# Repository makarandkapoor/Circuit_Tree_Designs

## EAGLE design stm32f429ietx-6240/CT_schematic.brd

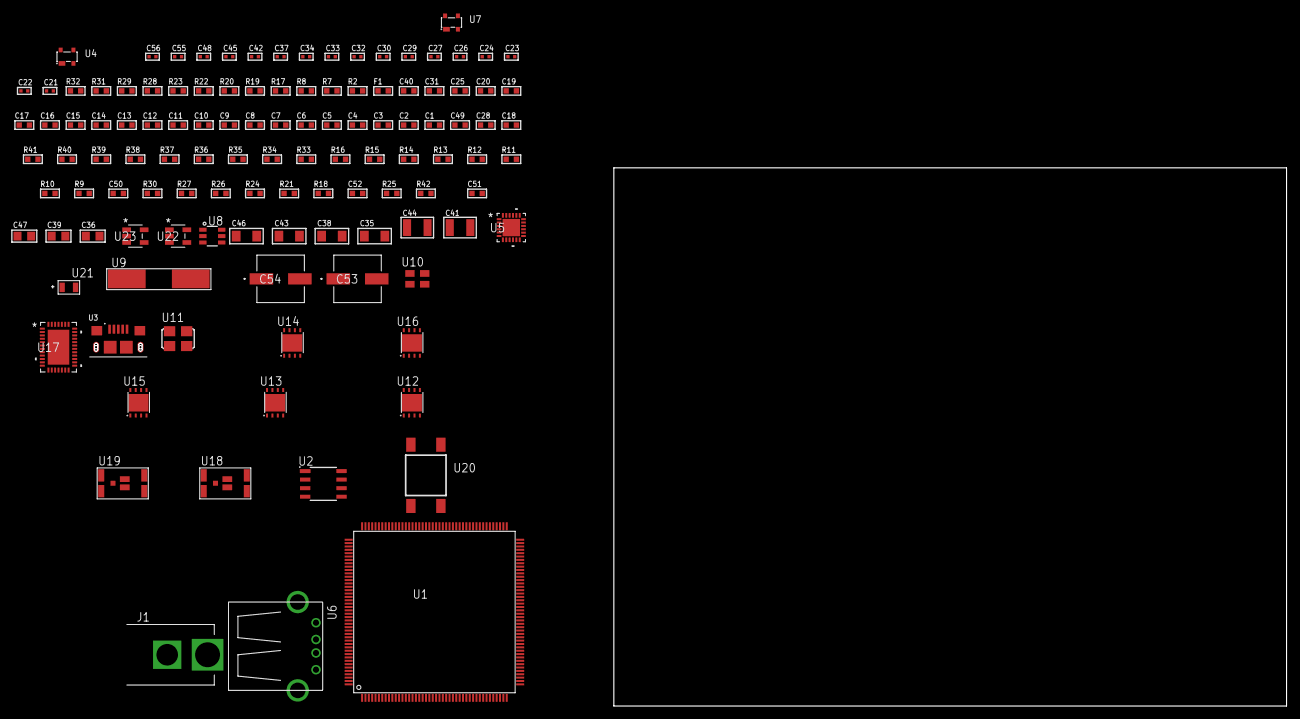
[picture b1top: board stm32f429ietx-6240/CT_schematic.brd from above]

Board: 2 copper layers, 118 parts (0 on the bottom side), 79 nets, no tracks yet.

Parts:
C1, C20, C25, C40: 1e-06; C0603
C2, C3, C4, C5, C6, C7, C8, C9, C10, C11, C12, C13, C14, C15, C16, C17: 1e-07; C0603
C18: 4.7e-06; C0603
C19: 1e-08; C0603
C21, C22, C48: 1e-07; C0402
C23, C24: 1e-11; C0402
C26, C27, C29, C30, C32, C33, C34, C37, C42, C45, C55, C56: 1e-08; C0402
C28, C49: 2.2e-06; C0603
C31: 0.0001; R0603
C35, C38, C43, C46: 1e-05; C1206
C36, C39, C47: 1e-05; C0805
C41, C44: 1e-05; C1210
C50: 2.45e-08; R0603
C51: 2.8258362168397e-09; R0603
C52: 7.105e-09; R0603
C53, C54: 0.0001; EXV-9H
F1: 240.0; L0603
J1: PJ-037B; PJ-037B_PACKAGE
R2, R20, R23, R29, R32: 1000.0; R0603
R7, R8: 4700.0; R0603
R9, R10, R11, R12, R13, R14, R15, R33, R35, R36, R39, R40, R41: 10000.0; R0603
R16: 47000.0; R0603
R17: 8060.0; R0603
R18, R21, R24, R26, R27, R30: 100000.0; R0603
R19, R31: 200.0; R0603
R22: 806.0; R0603
R25: 153694.38; R0603
R28: 3900.0; R0603
R34: 75000.0; R0603
R37, R38: 95300.0; R0603
R42: 65036.363636364; R0603
U1: STM32F429IET6; LQFP176
U2: AT25M02-SSHD-T; SOIC-8
U3: 10118193-0001LF; FCI_10118193-0001LF
U4, U7: prtr5v0u2ax; SOT143B
U5: USB3317C-CP-TR; QFN-24
U6: 61400416021; USB-A-H
U8: MAX4995AAUT+T; SOT-23-6
U9: ABLS-25.000MHZ-B2F-T
U10: ASEK-32.768KHz-ECST; ASEK
U11: ASFL1-26MHZ-NCS; ASFL1
U12, U13, U15, U16: LP3878SDX-ADJ/NOPB; WSON-8
U14: LP2951ACSDX/NOPB; WSON-8
U17: LTC2928CUHF#PBF; QFN-38_UHF
U18, U19: IRF8306MTRPbF; IRF8306MTRPBF
U20: 4-1437565-2; SW_4-1437565-2
U21: Q65110A2395; LGM67K-G1J2-24-Z
U22, U23: nc7sz125m5x; NC7SZ125M5X

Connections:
CLK_CRYSTAL_U1_29: C23.1, U1.29, U9.1
CLK_CRYSTAL_U1_30: C24.1, U1.30, U9.2
CLK_U1_9: U1.9, U10.3
CLK_U5_23: U5.23, U11.3
GND: C1.2, C2.2, C3.2, C4.2, C5.2, C6.2, C7.2, C8.2, C9.2, C10.2, C11.2, C12.2, C13.2, C14.2, C15.2, C16.2, C17.2, C18.2, C19.2, C20.2, C21.2, C22.2, C23.2, C24.2, C25.2, C26.2, C27.2, C28.2, C29.2, C30.2, C31.2, C32.2, C33.2, C34.2, C35.2, C36.2, C37.2, C38.2, C39.2, C40.2, C41.2, C42.2, C43.2, C44.2, C45.2, C46.2, C47.2, C48.2, C49.2, C50.2, C51.2, C52.2, C53.2, C54.2, C55.2, C56.2, J1.2, R2.2, R11.2, R16.2, R17.2, R20.2, R23.2, R26.2, R29.2, R32.2, R34.2, R37.2, R38.2, R39.2, R40.2, R41.2, U1.14, U1.22, U1.37, U1.61, U1.71, U1.90, U1.102, U1.113, U1.122, U1.126, U1.135, U1.148, U1.158, U2.4, U3.5, U3.6, U3.7, U3.8, U3.9, U4.1, U5.1, U5.25, U6.4, U6.5, U6.6, U7.1, U8.2, U10.2, U11.2, U12.3, U12.PAD, U13.3, U13.PAD, U14.3, U14.4, U14.PAD, U15.3, U15.PAD, U16.3, U16.PAD, U17.8, U17.9, U17.10, U17.12, U17.13, U17.24, U17.25, U17.30, U17.32, U17.39, U21.C, U22.1, U22.3, U23.1, U23.3
NET_U1_31: R7.1, U1.31, U22.4
NET_U1_39: C19.1, C20.1, F1.1, U1.38, U1.39
NET_U1_48: R12.1, U1.48
NET_U1_58: R11.1, U1.58
NET_U1_125: C22.1, U1.125
NET_U1_166: R10.1, U1.166
NET_U1_171: R9.1, U1.171
NET_U1_176: U20.3, U20.4
NET_U2_3: R13.1, U2.3
NET_U2_7: R15.1, U2.7
NET_U5_4: C28.1, U5.4
NET_U5_22: R8.1, U5.22, U23.4
NET_U5_24: R17.1, U5.24
NET_U6_1: C31.1, U5.2, U6.1, U7.4, U8.1
NET_U6_2: U5.5, U6.2, U7.3
NET_U6_3: U5.6, U6.3, U7.2
NET_U8_3: R16.1, U8.3
NET_U8_4: U5.7, U8.4
NET_U12_1: C34.1, U12.1
NET_U12_6: R19.2, R20.1, U12.6
NET_U12_8: R18.1, U12.8
NET_U13_1: C37.1, U13.1
NET_U13_6: R22.2, R23.1, U13.6
NET_U13_8: R21.1, U13.8
NET_U14_5: R24.1, U14.5
NET_U14_7: R25.2, R26.1, U14.7
NET_U15_1: C42.1, U15.1
NET_U15_6: R28.2, R29.1, U15.6
NET_U15_8: R27.1, U15.8
NET_U16_1: C45.1, U16.1
NET_U16_6: R31.2, R32.1, U16.6
NET_U16_8: R30.1, U16.8
NET_U17_3: R40.1, U17.3
NET_U17_6: R37.1, U17.6
NET_U17_7: R38.1, U17.7
NET_U17_16: R39.1, R42.1, U17.16
NET_U17_18: R36.1, U17.18
NET_U17_19: R35.1, U17.19, U17.20
NET_U17_21: R33.1, R34.1, U17.21, U22.2, U23.2
NET_U17_22: C48.1, R33.2, R35.2, R36.2, U17.11, U17.22
NET_U17_26: C51.1, U17.26
NET_U17_27: C50.1, U17.27
NET_U17_28: C52.1, U17.28
NET_U17_38: R41.1, U17.38
NET_U18_3: U17.2, U18.3
NET_U19_3: U17.37, U19.3
NET_U20_1: R2.1, U20.1, U20.2
PROC_SPI1_MISO: U1.52, U2.2
PROC_SPI1_MOSI: U1.53, U2.5
PROC_SPI1_NSS: R14.1, U1.50, U2.1
PROC_SPI1_SCK: U1.161, U2.6
PROC_USB_OTG_FS_DM: U1.122, U3.2, U4.3
PROC_USB_OTG_FS_DP: U1.123, U3.3, U4.2
PROC_USB_OTG_FS_VBUS: C25.1, U1.120, U3.1, U4.4
PROC_USB_OTG_HS_ULPI_CK: U1.51, U5.12
PROC_USB_OTG_HS_ULPI_D0: U1.47, U5.16
PROC_USB_OTG_HS_ULPI_D1: U1.56, U5.15
PROC_USB_OTG_HS_ULPI_D2: U1.57, U5.14
PROC_USB_OTG_HS_ULPI_D3: U1.79, U5.13
PROC_USB_OTG_HS_ULPI_D4: U1.80, U5.11
PROC_USB_OTG_HS_ULPI_D5: U1.92, U5.10
PROC_USB_OTG_HS_ULPI_D6: U1.93, U5.9
PROC_USB_OTG_HS_ULPI_D7: U1.163, U5.8
PROC_USB_OTG_HS_ULPI_DIR: U1.13, U5.19
PROC_USB_OTG_HS_ULPI_NXT: U1.35, U5.18
PROC_USB_OTG_HS_ULPI_STP: U1.32, U5.20
VCC_8V4: C49.1, C53.1, C54.1, J1.1, R42.2, U17.23, U18.1, U18.2, U18.6, U18.7, U19.1, U19.2, U19.6, U19.7
VCC_S1_8V4: C35.1, C38.1, C40.1, C43.1, R18.2, R21.2, R27.2, U12.4, U13.4, U14.8, U15.4, U18.4, U18.5
VCC_S2_8V4: C46.1, R30.2, U16.4, U19.4, U19.5
VCC_TIER1_1V2: C21.1, C36.1, R19.1, U1.81, U12.5
VCC_TIER1_1V8: C1.1, C2.1, C3.1, C4.1, C5.1, C6.1, C7.1, C8.1, C9.1, C10.1, C11.1, C12.1, C13.1, C14.1, C15.1, C16.1, C17.1, C18.1, C26.1, C29.1, C30.1, C39.1, C55.1, C56.1, F1.2, R7.2, R8.2, R9.2, R10.2, R12.2, R13.2, R14.2, R15.2, R22.1, U1.6, U1.15, U1.23, U1.36, U1.49, U1.62, U1.72, U1.82, U1.91, U1.103, U1.114, U1.127, U1.136, U1.149, U1.159, U1.172, U2.8, U5.17, U5.21, U13.5, U22.5, U23.5
VCC_TIER1_3V3: C27.1, C32.1, C33.1, C41.1, R24.2, R25.1, U5.3, U10.4, U11.4, U14.1
VCC_TIER1_5V0: C44.1, R28.1, U8.5, U15.5
VCC_TIER2_1V2: C47.1, R31.1, U16.5

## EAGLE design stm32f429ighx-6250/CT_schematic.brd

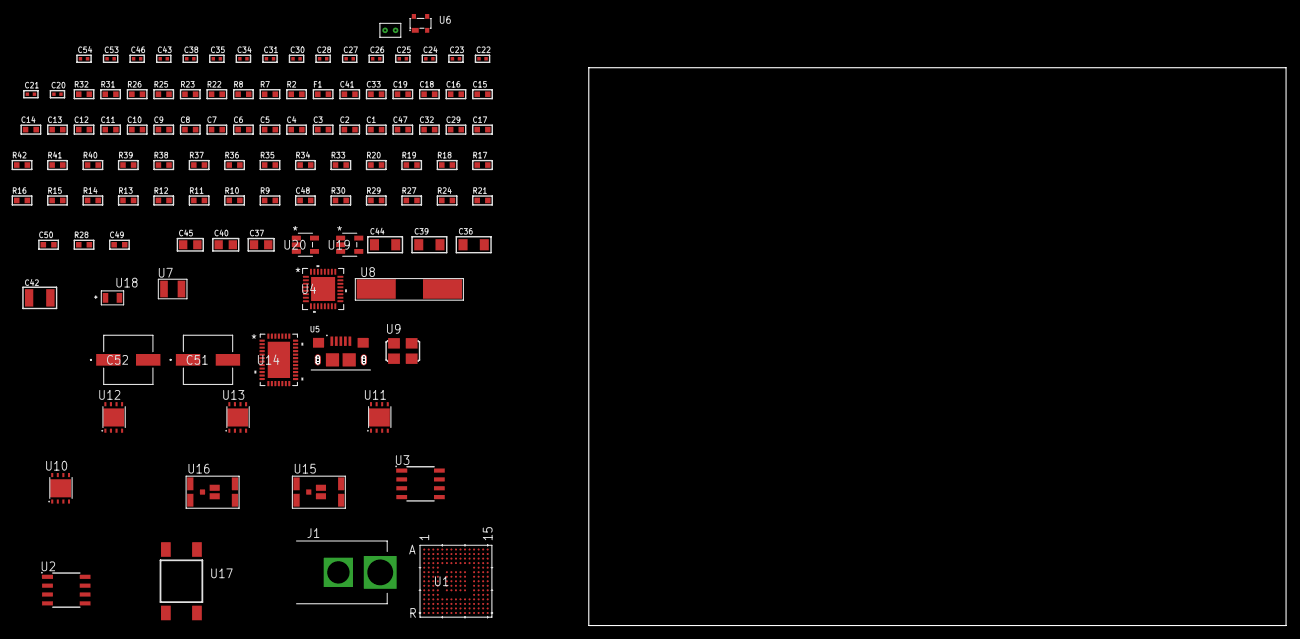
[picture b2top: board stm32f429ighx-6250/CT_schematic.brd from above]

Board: 2 copper layers, 114 parts (0 on the bottom side), 80 nets, no tracks yet.

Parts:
C1, C19, C33, C41: 1e-06; C0603
C2, C3, C4, C5, C6, C7, C8, C9, C10, C11, C12, C13, C14, C15, C16: 1e-07; C0603
C17: 4.7e-06; C0603
C18: 1e-08; C0603
C20, C21, C28, C30, C31, C46: 1e-07; C0402
C22, C23, C24, C25: 1e-11; C0402
C26, C27, C34, C35, C38, C43, C53, C54: 1e-08; C0402
C29, C32, C47: 2.2e-06; C0603
C36, C39, C44: 1e-05; C1206
C37, C40, C45: 1e-05; C0805
C42: 1e-05; C1210
C48: 2.45e-08; R0603
C49: 2.8258362168397e-09; R0603
C50: 7.105e-09; R0603
C51, C52: 0.0001; EXV-9H
F1: 240.0; L0603
J1: PJ-037B; PJ-037B_PACKAGE
R2, R23, R26, R32: 1000.0; R0603
R7, R8: 4700.0; R0603
R9, R10, R11, R12, R13, R14, R15, R16, R17, R18, R19, R20, R33, R35, R36, R39, R40, R41: 10000.0; R0603
R21, R24, R27, R29, R30: 100000.0; R0603
R22, R31: 200.0; R0603
R25: 806.0; R0603
R28: 153694.38; R0603
R34: 75000.0; R0603
R37, R38: 95300.0; R0603
R42: 62000.0; R0603
U1: STM32F429IGH6; UFBGA176_25
U2: AT25256B-SSHL-T; SOIC-8
U3: AT25320B-SSHL-T; SOIC-8
U4: TUSB1210BRHBR; RHB32_3P45X3P45
U5: 10118193-0001LF; FCI_10118193-0001LF
U6: prtr5v0u2ax; SOT143B
U7: ABS07-32.768KHZ-7-T
U8: ABLS-25.000MHZ-B2F-T
U9: ASFL1-26MHZ-NCS; ASFL1
U10, U11, U13: LP3878SDX-ADJ/NOPB; WSON-8
U12: LP2951ACSDX/NOPB; WSON-8
U14: LTC2928CUHF#PBF; QFN-38_UHF
U15, U16: IRF8306MTRPbF; IRF8306MTRPBF
U17: 4-1437565-2; SW_4-1437565-2
U18: Q65110A2395; LGM67K-G1J2-24-Z
U19, U20: nc7sz125m5x; NC7SZ125M5X
U21: Dummy; DUMMY_PACKAGE_252

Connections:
CLK_CRYSTAL_U1_E1: C22.1, U1.E1, U7.1
CLK_CRYSTAL_U1_F1: C23.1, U1.F1, U7.2
CLK_CRYSTAL_U1_G1: C24.1, U1.G1, U8.1
CLK_CRYSTAL_U1_H1: C25.1, U1.H1, U8.2
CLK_U4_1: U4.1, U9.3
GND: C1.2, C2.2, C3.2, C4.2, C5.2, C6.2, C7.2, C8.2, C9.2, C10.2, C11.2, C12.2, C13.2, C14.2, C15.2, C16.2, C17.2, C18.2, C19.2, C20.2, C21.2, C22.2, C23.2, C24.2, C25.2, C26.2, C27.2, C28.2, C29.2, C30.2, C31.2, C32.2, C33.2, C34.2, C35.2, C36.2, C37.2, C38.2, C39.2, C40.2, C41.2, C42.2, C43.2, C44.2, C45.2, C46.2, C47.2, C48.2, C49.2, C50.2, C51.2, C52.2, C53.2, C54.2, J1.2, R2.2, R23.2, R26.2, R29.2, R32.2, R34.2, R37.2, R38.2, R39.2, R40.2, R41.2, U1.D5, U1.D7, U1.D8, U1.D9, U1.F2, U1.F6, U1.F7, U1.F8, U1.F9, U1.F10, U1.F12, U1.G2, U1.G6, U1.G7, U1.G8, U1.G9, U1.G10, U1.G12, U1.H6, U1.H7, U1.H8, U1.H9, U1.H10, U1.H12, U1.J6, U1.J7, U1.J8, U1.J9, U1.J10, U1.K6, U1.K7, U1.K8, U1.K9, U1.K10, U1.M1, U1.M8, U1.M9, U1.N1, U2.4, U3.4, U4.33, U5.5, U5.6, U5.7, U5.8, U5.9, U6.1, U9.2, U10.3, U10.PAD, U11.3, U11.PAD, U12.3, U12.4, U12.PAD, U13.3, U13.PAD, U14.8, U14.9, U14.10, U14.12, U14.13, U14.24, U14.25, U14.30, U14.32, U14.39, U18.C, U19.1, U19.3, U20.1, U20.3, U21.1
NET_U1_C6: R9.1, U1.C6
NET_U1_D6: R10.1, U1.D6
NET_U1_F13: C21.1, U1.F13
NET_U1_J1: R7.1, U1.J1, U19.4
NET_U1_L4: R12.1, U1.L4
NET_U1_M6: R11.1, U1.M6
NET_U1_R1: C18.1, C19.1, F1.1, U1.P1, U1.R1
NET_U1_R15: U17.3, U17.4
NET_U2_3: R13.1, U2.3
NET_U2_7: R15.1, U2.7
NET_U3_3: R16.1, U3.3
NET_U3_7: R18.1, U3.7
NET_U4_11: R19.1, U4.11
NET_U4_12: C32.1, U4.12
NET_U4_14: R20.1, U4.14
NET_U4_20: C29.1, U4.20
NET_U4_27: R8.1, U4.27, U20.4
NET_U5_1: C33.1, U4.22, U5.1, U6.4
NET_U5_2: U4.19, U5.2, U6.3
NET_U5_3: U4.18, U5.3, U6.2
NET_U10_1: C35.1, U10.1
NET_U10_6: R22.2, R23.1, U10.6
NET_U10_8: R21.1, U10.8
NET_U11_1: C38.1, U11.1
NET_U11_6: R25.2, R26.1, U11.6
NET_U11_8: R24.1, U11.8
NET_U12_5: R27.1, U12.5
NET_U12_7: R28.2, R29.1, U12.7
NET_U13_1: C43.1, U13.1
NET_U13_6: R31.2, R32.1, U13.6
NET_U13_8: R30.1, U13.8
NET_U14_3: R40.1, U14.3
NET_U14_6: R37.1, U14.6
NET_U14_7: R38.1, U14.7
NET_U14_16: R39.1, R42.1, U14.16
NET_U14_18: R36.1, U14.18
NET_U14_19: R35.1, U14.19, U14.20
NET_U14_21: R33.1, R34.1, U14.21, U19.2, U20.2
NET_U14_22: C46.1, R33.2, R35.2, R36.2, U14.11, U14.22
NET_U14_26: C49.1, U14.26
NET_U14_27: C48.1, U14.27
NET_U14_28: C50.1, U14.28
NET_U14_38: R41.1, U14.38
NET_U15_3: U14.2, U15.3
NET_U16_3: U14.37, U16.3
NET_U17_1: R2.1, U17.1, U17.2
PROC_DAC_OUT1: U1.N4, U21.2
PROC_SPI1_MISO: U1.A9, U2.2
PROC_SPI1_MOSI: U1.R3, U2.5
PROC_SPI1_NSS: R14.1, U1.A13, U2.1
PROC_SPI1_SCK: U1.A10, U2.6
PROC_SPI2_MISO: U1.C14, U3.2
PROC_SPI2_MOSI: U1.C13, U3.5
PROC_SPI2_NSS: R17.1, U1.B4, U3.1
PROC_SPI2_SCK: U1.D11, U3.6
PROC_USB_OTG_HS_ULPI_CK: U1.P4, U4.26
PROC_USB_OTG_HS_ULPI_D0: U1.R2, U4.3
PROC_USB_OTG_HS_ULPI_D1: U1.R5, U4.4
PROC_USB_OTG_HS_ULPI_D2: U1.R4, U4.5
PROC_USB_OTG_HS_ULPI_D3: U1.R12, U4.6
PROC_USB_OTG_HS_ULPI_D4: U1.R13, U4.7
PROC_USB_OTG_HS_ULPI_D5: U1.P12, U4.9
PROC_USB_OTG_HS_ULPI_D6: U1.P13, U4.10
PROC_USB_OTG_HS_ULPI_D7: U1.A6, U4.13
PROC_USB_OTG_HS_ULPI_DIR: U1.E4, U4.31
PROC_USB_OTG_HS_ULPI_NXT: U1.H4, U4.2
PROC_USB_OTG_HS_ULPI_STP: U1.M2, U4.29
VCC_7V8: C47.1, C51.1, C52.1, J1.1, R42.2, U14.23, U15.1, U15.2, U15.6, U15.7, U16.1, U16.2, U16.6, U16.7
VCC_S1_7V8: C36.1, C39.1, C41.1, R21.2, R24.2, U10.4, U11.4, U12.8, U15.4, U15.5
VCC_S2_7V8: C44.1, R30.2, U13.4, U16.4, U16.5
VCC_TIER1_1V2: C20.1, C37.1, R22.1, U1.M10, U10.5
VCC_TIER1_1V8: C1.1, C2.1, C3.1, C4.1, C5.1, C6.1, C7.1, C8.1, C9.1, C10.1, C11.1, C12.1, C13.1, C14.1, C15.1, C16.1, C17.1, C26.1, C27.1, C30.1, C31.1, C40.1, C53.1, C54.1, F1.2, R7.2, R8.2, R9.2, R10.2, R11.2, R12.2, R13.2, R14.2, R15.2, R16.2, R17.2, R18.2, R19.2, R20.2, R25.1, U1.C1, U1.C5, U1.C7, U1.C8, U1.C9, U1.F3, U1.G3, U1.G13, U1.H13, U1.J12, U1.J13, U1.K4, U1.N8, U1.N9, U1.N10, U2.8, U3.8, U4.28, U4.30, U4.32, U11.5, U19.5, U20.5
VCC_TIER1_3V3: C28.1, C34.1, C42.1, R27.2, R28.1, U4.21, U9.4, U12.1
VCC_TIER2_1V2: C45.1, R31.1, U13.5

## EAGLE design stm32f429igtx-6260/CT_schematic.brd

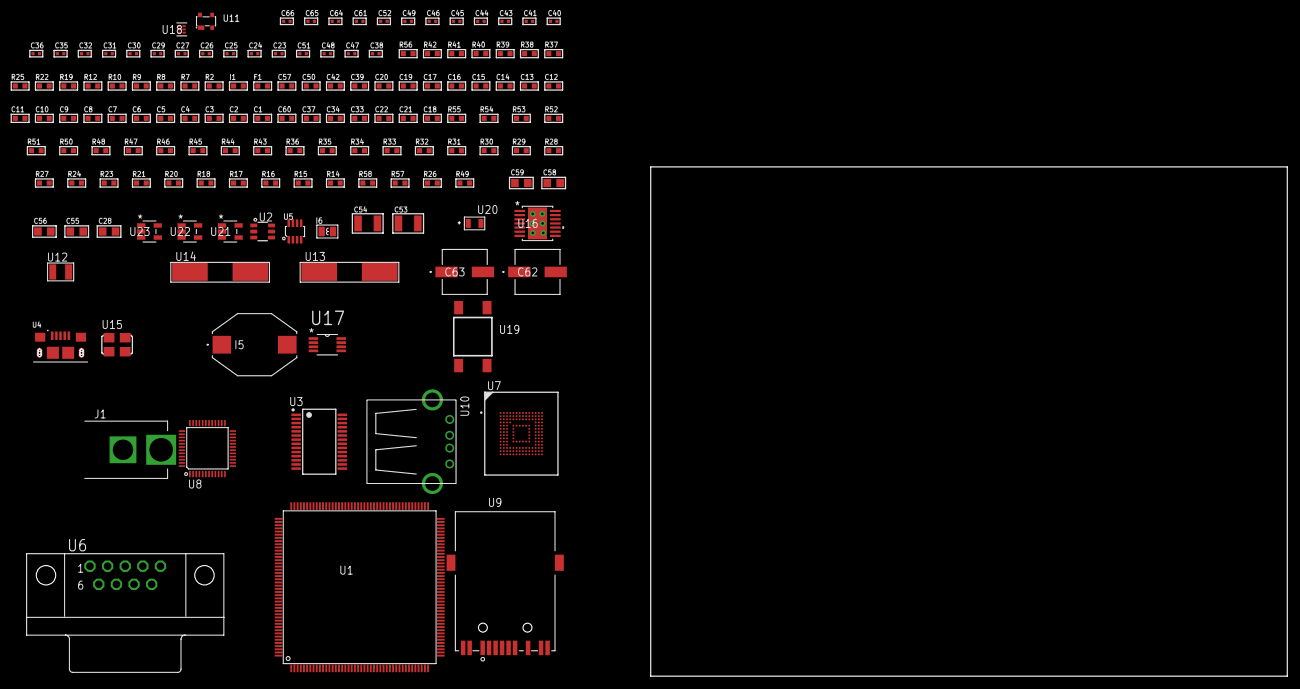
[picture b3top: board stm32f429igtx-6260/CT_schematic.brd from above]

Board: 2 copper layers, 145 parts (0 on the bottom side), 100 nets, no tracks yet.

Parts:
C1, C20, C39, C42, C50, C57: 1e-06; C0603
C2, C3, C4, C5, C6, C7, C8, C9, C10, C11, C12, C13, C14, C15, C16, C17: 1e-07; C0603
C18: 4.7e-06; C0603
C19: 1e-08; C0603
C21, C22, C33, C34, C37: 2.2e-06; C0603
C23, C24, C25, C26: 1e-11; C0402
C27, C29, C30, C31, C32, C35, C36, C40, C43, C45, C46, C52, C61: 1e-07; C0402
C28: 4.7e-06; C0805
C38: 2.2e-08; C0402
C41, C44, C49, C64, C65, C66: 1e-08; C0402
C47, C48: 2.7e-11; C0402
C51: 3.3e-09; C0402
C53, C54: 2.2e-05; C1210
C55, C56, C58, C59: 1e-05; C0805
C60: 1.6e-09; C0603
C62, C63: 0.0001; EXV-9H
F1: 240.0; L0603
I1: 97.0; R0603
I5: 1.5e-06; IND_PM3316
I6: 3.3e-06; L0806
J1: PJ-037B; PJ-037B_PACKAGE
R2: 1000.0; R0603
R7, R8, R9, R22, R42: 4700.0; R0603
R10, R12: 2200.0; R0603
R14, R51: 47000.0; R0603
R15, R16, R17, R18, R20, R21, R23, R24, R43, R44, R45, R46, R47, R48, R54, R55: 10000.0; R0603
R19: 1270.0; R0603
R25: 120.0; R0603
R26: 100000.0; R0603
R27, R28, R29, R30, R31, R32, R33, R34, R35, R36: 34000.0; R0603
R37, R38: 0.1; R0603
R39, R40: 200.0; R0603
R41: 2490.0; R0603
R49: 71007.101651032; R0603
R50: 22000.0; R0603
R52: 56000.0; R0603
R53: 18000.0; R0603
R56: 9100.0; R0603
R57: 680000.0; R0603
R58: 120000.0; R0603
U1: STM32F429IGT6; LQFP176
U2: MAX4995AAUT+T; SOT-23-6
U3: FT232RL-REEL; SSOP-28
U4: 10118193-0001LF; FCI_10118193-0001LF
U5: MAX3051EKA+T; SOT-23-8
U6: 182-009-113R531; 182-009-MALE
U7: mtfc4gmcdm; TFBGA-153
U8: RTL8201FL-VB-CG
U9: 7498011122R
U10: 61400416021; USB-A-H
U11: prtr5v0u2ax; SOT143B
U12: ABS07-32.768KHZ-7-T
U13, U14: ABLS-25.000MHZ-B2F-T
U15: ASFL1-12MHZ-NCS; ASFL1
U16: tps54325PWP; HTSSOP14
U17: TPS61085DGKR; MSOP-8
U18: TPS3895ADRYR; SON-6
U19: 4-1437565-2; SW_4-1437565-2
U20: Q65110A2395; LGM67K-G1J2-24-Z
U21, U22, U23: nc7sz125m5x; NC7SZ125M5X

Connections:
CLK_CRYSTAL_U1_9: C23.1, U1.9, U12.1
CLK_CRYSTAL_U1_10: C24.1, U1.10, U12.2
CLK_CRYSTAL_U1_29: C25.1, U1.29, U13.1
CLK_CRYSTAL_U1_30: C26.1, U1.30, U13.2
CLK_CRYSTAL_U8_42: C48.1, U8.42, U14.1
CLK_CRYSTAL_U8_43: C47.1, U8.43, U14.2
CLK_U3_27: U3.27, U15.3
GND: C1.2, C2.2, C3.2, C4.2, C5.2, C6.2, C7.2, C8.2, C9.2, C10.2, C11.2, C12.2, C13.2, C14.2, C15.2, C16.2, C17.2, C18.2, C19.2, C20.2, C21.2, C22.2, C23.2, C24.2, C25.2, C26.2, C27.2, C28.2, C29.2, C30.2, C31.2, C32.2, C33.2, C34.2, C35.2, C36.2, C37.2, C38.2, C39.2, C40.2, C41.2, C42.2, C43.2, C44.2, C45.2, C46.2, C47.2, C48.2, C49.2, C50.2, C51.2, C53.2, C54.2, C55.2, C56.2, C57.2, C58.2, C59.1, C59.2, C60.1, C60.2, C61.2, C62.2, C63.2, C64.2, C65.2, C66.2, J1.2, R2.2, R14.2, R17.2, R18.2, R19.2, R21.2, R24.2, R26.2, R37.2, R38.2, R41.2, R43.2, R44.2, R46.2, R50.2, R53.2, R56.2, R58.2, U1.14, U1.22, U1.37, U1.61, U1.71, U1.90, U1.102, U1.113, U1.126, U1.135, U1.148, U1.158, U2.2, U3.7, U3.18, U3.21, U3.25, U3.26, U4.5, U4.6, U4.7, U4.8, U4.9, U5.2, U6.5, U7.C4, U7.E7, U7.G5, U7.H10, U7.K8, U7.N2, U7.N5, U7.P4, U7.P6, U8.7, U8.20, U8.33, U8.47, U9.9, U10.4, U10.5, U10.6, U11.1, U15.2, U16.5, U16.8, U16.9, U16.15, U17.4, U18.2, U20.C, U21.1, U21.3, U22.1, U22.3, U23.1, U23.3
NET_U1_31: R9.1, U1.31, U23.4
NET_U1_33: R10.1, U1.33, U8.30
NET_U1_39: C19.1, C20.1, F1.1, U1.38, U1.39
NET_U1_42: R12.1, U1.42, U8.31
NET_U1_48: R18.1, U1.48
NET_U1_58: R17.1, U1.58
NET_U1_81: C21.1, U1.81
NET_U1_121: R19.1, U1.121
NET_U1_125: C22.1, U1.125
NET_U1_166: R16.1, U1.166
NET_U1_171: R15.1, U1.171
NET_U1_176: U19.3, U19.4
NET_U2_3: R14.1, U2.3
NET_U3_14: R23.1, U3.14
NET_U3_17: C29.1, U3.17
NET_U3_19: R24.1, U3.19
NET_U4_1: R22.1, U4.1
NET_U4_2: U3.16, U4.2
NET_U4_3: U3.15, U4.3
NET_U5_6: R25.2, U5.6
NET_U5_8: R26.1, U5.8
NET_U6_2: R25.2, U5.6, U6.2
NET_U6_3: R25.1, U5.7, U6.3
NET_U7_C2: C34.1, C35.1, U7.C2
NET_U7_K5: R8.1, U7.K5, U22.4
NET_U8_6: C39.1, C40.1, C41.1, I1.1, U8.6, U8.41
NET_U8_10: R46.1, U8.10
NET_U8_29: R7.1, U8.29, U21.4
NET_U8_32: R42.1, U8.32
NET_U8_34: R44.1, U8.34
NET_U8_35: R45.1, U8.35
NET_U8_40: C46.1, U8.40
NET_U8_46: R41.1, U8.46
NET_U8_48: C45.1, U8.48
NET_U9_1: U8.1, U9.1
NET_U9_3: U8.2, U9.3
NET_U9_4: U8.4, U9.4
NET_U9_5: C38.1, U9.2, U9.5
NET_U9_6: U8.5, U9.6
NET_U9_8: R38.1, U9.8
NET_U9_10: R39.1, U9.10
NET_U9_12: R40.1, U9.12
NET_U9_13: R37.1, U9.13, U9.14
NET_U16_2: R49.2, R50.1, U16.2
NET_U16_3: C50.1, U16.3
NET_U16_4: C51.1, U16.4
NET_U16_10: C52.1, I5.1, U16.10, U16.11
NET_U16_12: C52.2, U16.12
NET_U17_1: R51.1, U17.1
NET_U17_2: R52.1, R53.1, U17.2
NET_U17_5: I6.1, U17.5
NET_U18_1: R55.1, R56.1, U18.1
NET_U18_3: R57.2, R58.1, U18.3
NET_U18_4: R54.1, U18.4, U21.2, U22.2, U23.2
NET_U19_1: R2.1, U19.1, U19.2
PROC_CAN1_RX: U1.11, U5.4
PROC_CAN1_TX: U1.128, U5.1
PROC_ETH_COL: U1.44, U8.38
PROC_ETH_CRS: U1.40, U8.36
PROC_ETH_RXD0: U1.54, U8.14
PROC_ETH_RXD1: U1.55, U8.16
PROC_ETH_RXD2: U1.56, U8.17
PROC_ETH_RXD3: R47.1, U1.57, U8.18
PROC_ETH_RX_CLK: U1.41, U8.19
PROC_ETH_RX_DV: R43.1, U1.53, U8.13
PROC_ETH_RX_ER: R48.1, U1.12, U8.39
PROC_ETH_TXD0: U1.92, U8.23
PROC_ETH_TXD1: U1.93, U8.24
PROC_ETH_TXD2: U1.34, U8.25
PROC_ETH_TXD3: U1.1, U8.26
PROC_ETH_TX_CLK: U1.35, U8.22
PROC_ETH_TX_EN: U1.80, U8.27
PROC_GPIO_TO_U1_USB_FAULT: R20.1, U1.3, U2.6
PROC_GPIO_TO_U1_VBUS_EN: R21.1, U1.2, U2.4
PROC_SDIO_CK: R36.1, U1.141, U7.M6
PROC_SDIO_CMD: R35.1, U1.144, U7.M5
PROC_SDIO_D0: R27.1, U1.117, U7.A3
PROC_SDIO_D1: R28.1, U1.118, U7.A4
PROC_SDIO_D2: R29.1, U1.139, U7.A5
PROC_SDIO_D3: R30.1, U1.140, U7.B2
PROC_SDIO_D4: R31.1, U1.167, U7.B3
PROC_SDIO_D5: R32.1, U1.168, U7.B4
PROC_SDIO_D6: R33.1, U1.115, U7.B5
PROC_SDIO_D7: R34.1, U1.116, U7.B6
PROC_UART7_RX: U1.24, U3.1
PROC_UART7_TX: U1.25, U3.5
PROC_USB_OTG_FS_DM: U1.122, U10.2, U11.3
PROC_USB_OTG_FS_DP: U1.123, U10.3, U11.2
PROC_USB_OTG_FS_VBUS: U1.120, U2.1, U10.1, U11.4
VCC_S1_4V5: C55.1, C56.1, C57.1, C58.1, C62.1, C63.1, I6.2, J1.1, U16.7, U16.13, U16.14, U17.3, U17.6
VCC_TIER1_3V3: C1.1, C2.1, C3.1, C4.1, C5.1, C6.1, C7.1, C8.1, C9.1, C10.1, C11.1, C12.1, C13.1, C14.1, C15.1, C16.1, C17.1, C18.1, C27.1, C28.1, C30.1, C31.1, C32.1, C33.1, C36.1, C37.1, C42.1, C43.1, C44.1, C49.1, C53.1, C54.1, C61.1, C64.1, C65.1, C66.1, F1.2, I1.2, I5.2, R7.2, R8.2, R9.2, R10.2, R12.2, R15.2, R16.2, R20.2, R23.2, R27.2, R28.2, R29.2, R30.2, R31.2, R32.2, R33.2, R34.2, R35.2, R36.2, R42.2, R45.2, R47.2, R48.2, R49.1, R54.2, R55.2, R57.1, U1.6, U1.15, U1.23, U1.36, U1.49, U1.62, U1.72, U1.82, U1.91, U1.103, U1.114, U1.127, U1.136, U1.149, U1.159, U1.172, U3.4, U3.20, U5.3, U7.C6, U7.E6, U7.F5, U7.J10, U7.K9, U7.M4, U7.N4, U7.P3, U7.P5, U8.15, U8.21, U8.37, U15.4, U16.1, U18.6, U21.5, U22.5, U23.5
VCC_TIER1_5V0: C59.2, R52.2, U2.5

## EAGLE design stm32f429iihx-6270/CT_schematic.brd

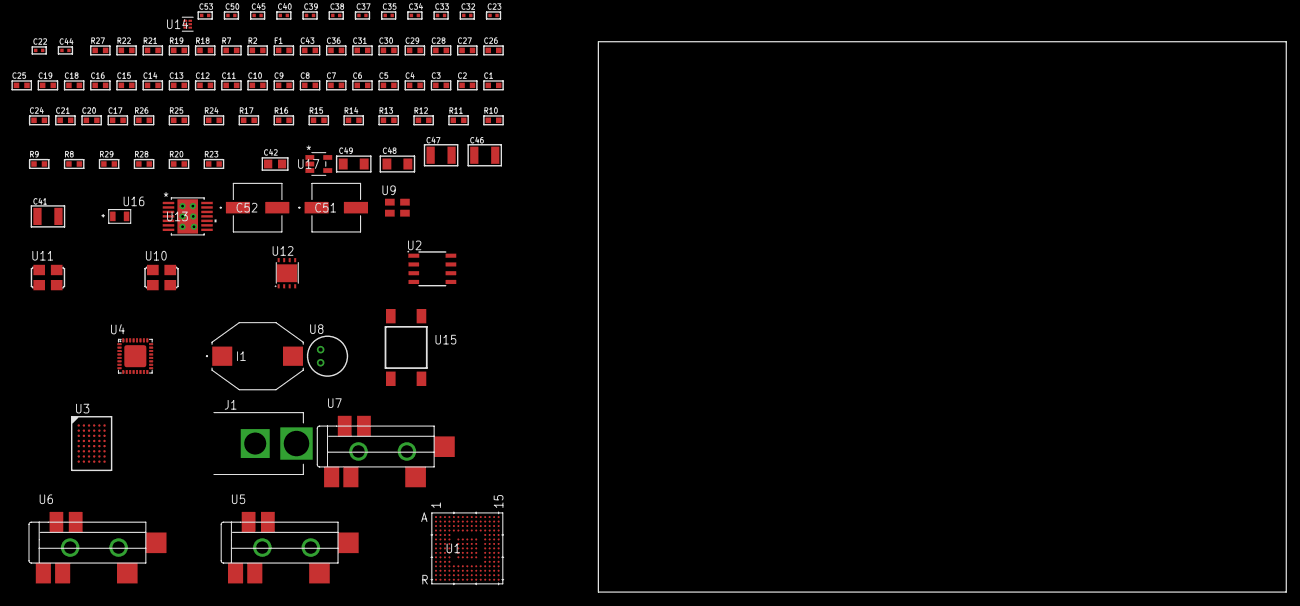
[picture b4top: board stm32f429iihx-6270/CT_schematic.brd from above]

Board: 2 copper layers, 100.0 x 80.0 mm, 97 parts (0 on the bottom side), 89 nets, no tracks yet.

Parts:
C1, C19, C25, C26, C27, C28, C29, C30, C31, C36, C43: 1e-06; C0603
C2, C3, C4, C5, C6, C7, C8, C9, C10, C11, C12, C13, C14, C15, C16: 1e-07; C0603
C17: 4.7e-06; C0603
C18: 1e-08; C0603
C20, C21, C24: 2.2e-06; C0603
C22, C37, C38, C39, C40, C53: 1e-08; C0402
C23, C32, C33, C34, C35, C45, C50: 1e-07; C0402
C41: 1e-05; C1210
C42: 1e-05; C0805
C44: 3.3e-09; C0402
C46, C47: 2.2e-05; C1210
C48, C49: 1e-05; C1206
C51, C52: 0.0001; EXV-9H
F1: 240.0; L0603
I1: 1e-05; IND_PM3316
J1: PJ-037B; PJ-037B_PACKAGE
R2, R22: 1000.0; R0603
R7: 4700.0; R0603
R8, R9, R10, R11, R12, R13, R14, R15, R16, R17, R25, R26: 10000.0; R0603
R18, R19: 1270.0; R0603
R20: 100000.0; R0603
R21: 200.0; R0603
R23: 71007.101651032; R0603
R24: 22000.0; R0603
R27: 9100.0; R0603
R28: 680000.0; R0603
R29: 120000.0; R0603
U1: STM32F429IIH6; UFBGA176_25
U2: AT25320B-SSHL-T; SOIC-8
U3: CY62147GE30-45BVXI; VFBGA48
U4: SGTL5000XNAA3; QFN-32
U5, U6, U7: SJ-43515TS-SMT-TR
U8: WM-64PCT; WM-64PC
U9: ASEK-32.768KHz-ECST; ASEK
U10: ASFL-24.57MHZ-NCS; ASFL1
U11: ASFL1-25MHZ-NCS; ASFL1
U12: LP3878SDX-ADJ/NOPB; WSON-8
U13: tps54225PWP; HTSSOP14
U14: TPS3895ADRYR; SON-6
U15: 4-1437565-2; SW_4-1437565-2
U16: Q65110A2395; LGM67K-G1J2-24-Z
U17: nc7sz125m5x; NC7SZ125M5X

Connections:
CLK_U1_E1: U1.E1, U9.3
CLK_U1_G1: U1.G1, U11.3
CLK_U4_21: U4.21, U10.3
GND: C1.2, C2.2, C3.2, C4.2, C5.2, C6.2, C7.2, C8.2, C9.2, C10.2, C11.2, C12.2, C13.2, C14.2, C15.2, C16.2, C17.2, C18.2, C19.2, C20.2, C21.2, C22.2, C23.2, C24.2, C32.2, C33.2, C34.2, C35.2, C36.2, C37.2, C38.2, C39.2, C40.2, C41.2, C42.2, C43.2, C44.2, C46.2, C47.2, C48.2, C49.2, C50.2, C51.2, C52.2, C53.2, J1.2, R2.2, R11.2, R19.2, R22.2, R24.2, R27.2, R29.2, U1.D5, U1.D7, U1.D8, U1.D9, U1.F2, U1.F6, U1.F7, U1.F8, U1.F9, U1.F10, U1.F12, U1.G2, U1.G6, U1.G7, U1.G8, U1.G9, U1.G10, U1.G12, U1.H6, U1.H7, U1.H8, U1.H9, U1.H10, U1.H12, U1.J6, U1.J7, U1.J8, U1.J9, U1.J10, U1.K6, U1.K7, U1.K8, U1.K9, U1.K10, U1.M1, U1.M8, U1.M9, U1.N1, U2.4, U3.D1, U3.E6, U4.1, U4.3, U4.7, U4.EXP, U6.1, U7.1, U8.2, U9.2, U10.2, U11.2, U12.3, U12.PAD, U13.5, U13.8, U13.9, U13.15, U14.2, U16.C, U17.1, U17.3
NET_U1_C6: R8.1, U1.C6
NET_U1_D6: R9.1, U1.D6
NET_U1_F13: C21.1, U1.F13
NET_U1_J1: R7.1, U1.J1, U17.4
NET_U1_L4: R11.1, U1.L4
NET_U1_M6: R10.1, U1.M6
NET_U1_M10: C20.1, U1.M10
NET_U1_R1: C18.1, C19.1, F1.1, U1.P1, U1.R1
NET_U1_R15: U15.3, U15.4
NET_U2_3: R12.1, U2.3
NET_U2_7: R14.1, U2.7
NET_U4_10: C35.1, U4.10
NET_U4_29: R18.1, U4.29
NET_U4_31: R19.1, U4.31
NET_U5_1: U4.4, U5.1
NET_U5_2: U4.2, U5.2
NET_U5_5: U4.6, U5.5
NET_U6_2: C26.1, U6.2
NET_U6_5: C25.1, U6.5
NET_U7_2: C28.1, C29.1, U7.2
NET_U7_5: C27.1, U7.5
NET_U7_13: C28.2, C29.2
NET_U8_1: C30.1, C31.1, C36.1, U4.16, U8.1
NET_U8_15: C30.2, C31.2
NET_U12_1: C40.1, U12.1
NET_U12_6: R21.2, R22.1, U12.6
NET_U12_8: R20.1, U12.8
NET_U13_2: R23.2, R24.1, U13.2
NET_U13_3: C43.1, U13.3
NET_U13_4: C44.1, U13.4
NET_U13_10: C45.1, I1.1, U13.10, U13.11
NET_U13_12: C45.2, U13.12
NET_U14_1: R26.1, R27.1, U14.1
NET_U14_3: R28.2, R29.1, U14.3
NET_U14_4: R25.1, U14.4, U17.2
NET_U15_1: R2.1, U15.1, U15.2
PROC_FMC_A0: U1.E2, U3.A3
PROC_FMC_A1: U1.H3, U3.A4
PROC_FMC_A2: U1.H2, U3.A5
PROC_FMC_A3: U1.J2, U3.B3
PROC_FMC_A4: U1.J3, U3.B4
PROC_FMC_A5: U1.K3, U3.C3
PROC_FMC_A6: U1.P6, U3.C4
PROC_FMC_A7: U1.N6, U3.D4
PROC_FMC_A8: U1.R7, U3.H2
PROC_FMC_A9: U1.P7, U3.H3
PROC_FMC_A10: U1.N7, U3.H4
PROC_FMC_A11: U1.M7, U3.H5
PROC_FMC_A12: U1.L15, U3.G3
PROC_FMC_A13: U1.K15, U3.G4
PROC_FMC_A14: U1.K14, U3.F3
PROC_FMC_A15: U1.K13, U3.F4
PROC_FMC_A16: U1.N14, U3.E4
PROC_FMC_A17: U1.N13, U3.D3
PROC_FMC_D0: U1.M14, U3.B6
PROC_FMC_D1: U1.L14, U3.C5
PROC_FMC_D2: U1.B12, U3.C6
PROC_FMC_D3: U1.C12, U3.D5
PROC_FMC_D4: U1.R8, U3.E5
PROC_FMC_D5: U1.P8, U3.F5
PROC_FMC_D6: U1.P9, U3.F6
PROC_FMC_D7: U1.R9, U3.G6
PROC_FMC_D8: U1.P10, U3.B1
PROC_FMC_D9: U1.R10, U3.C1
PROC_FMC_D10: U1.N11, U3.C2
PROC_FMC_D11: U1.P11, U3.D2
PROC_FMC_D12: U1.R11, U3.E2
PROC_FMC_D13: U1.P15, U3.F2
PROC_FMC_D14: U1.P14, U3.F1
PROC_FMC_D15: U1.N15, U3.G1
PROC_FMC_NBL0: U1.A4, U3.A1
PROC_FMC_NE2: R16.1, U1.C10, U3.B5
PROC_FMC_NOE: R15.1, U1.D10, U3.A2
PROC_FMC_NWE: R17.1, U1.C11, U3.G5
PROC_I2S2_CK: U1.D11, U4.24
PROC_I2S2_EXT_SD: U1.C14, U4.25
PROC_I2S2_SD: U1.C13, U4.26
PROC_I2S2_WS: U1.B4, U4.23
PROC_SPI1_MISO: U1.A9, U2.2
PROC_SPI1_MOSI: U1.A6, U2.5
PROC_SPI1_NSS: R13.1, U1.A13, U2.1
PROC_SPI1_SCK: U1.A10, U2.6
VCC_S1_15V9: C41.1, C48.1, C49.1, C51.1, C52.1, J1.1, R20.2, U12.4, U13.7, U13.13, U13.14
VCC_TIER1_1V2: C32.1, C42.1, R21.1, U4.30, U12.5
VCC_TIER1_3V3: C1.1, C2.1, C3.1, C4.1, C5.1, C6.1, C7.1, C8.1, C9.1, C10.1, C11.1, C12.1, C13.1, C14.1, C15.1, C16.1, C17.1, C22.1, C23.1, C24.1, C33.1, C34.1, C37.1, C38.1, C39.1, C46.1, C47.1, C50.1, C53.1, F1.2, I1.2, R7.2, R8.2, R9.2, R10.2, R12.2, R13.2, R14.2, R15.2, R16.2, R17.2, R18.2, R23.1, R25.2, R26.2, R28.1, U1.C1, U1.C5, U1.C7, U1.C8, U1.C9, U1.F3, U1.G3, U1.G13, U1.H13, U1.J12, U1.J13, U1.K4, U1.N8, U1.N9, U1.N10, U2.8, U3.D6, U3.E1, U4.5, U4.20, U9.4, U10.4, U11.4, U13.1, U14.6, U17.5

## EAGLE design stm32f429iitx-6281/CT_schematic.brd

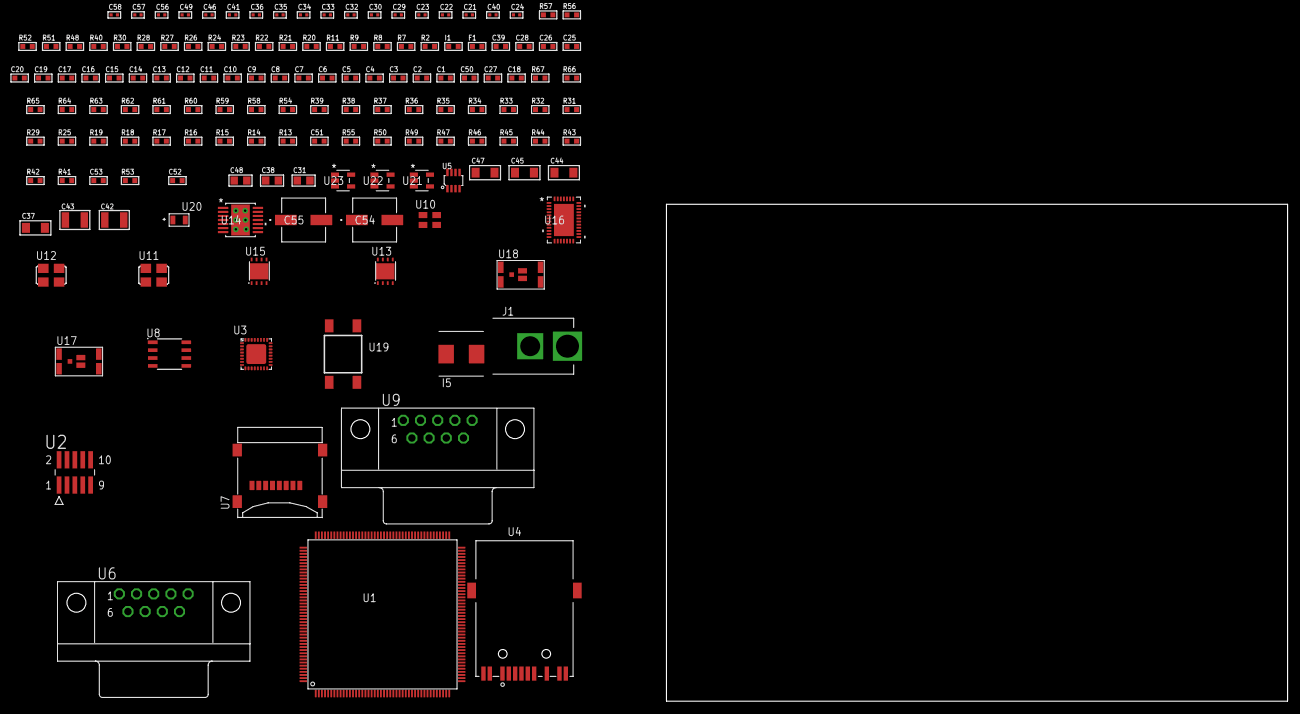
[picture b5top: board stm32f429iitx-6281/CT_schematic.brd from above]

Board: 2 copper layers, 100.0 x 80.0 mm, 145 parts (0 on the bottom side), 94 nets, no tracks yet.

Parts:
C1, C20, C25, C26, C28, C39: 1e-06; C0603
C2, C3, C4, C5, C6, C7, C8, C9, C10, C11, C12, C13, C14, C15, C16, C17: 1e-07; C0603
C18: 4.7e-06; C0603
C19: 1e-08; C0603
C21, C22, C23, C29, C30, C32, C41, C49: 1e-07; C0402
C24: 2.2e-08; C0402
C27: 4.7e-10; C0603
C31, C38, C48: 1e-05; C0805
C33, C34, C35, C36, C46, C56, C57, C58: 1e-08; C0402
C37, C44, C45, C47: 1e-05; C1206
C40: 3.3e-09; C0402
C42, C43: 2.2e-05; C1210
C50: 2.2e-06; C0603
C51: 2.45e-08; R0603
C52: 2.8258362168397e-09; R0603
C53: 7.105e-09; R0603
C54, C55: 0.0001; EXV-9H
F1: 240.0; L0603
I1: 97.0; R0603
I5: 3.3e-06; WE-HCI_7030/7040/7050
J1: PJ-037B; PJ-037B_PACKAGE
R2, R52, R57: 1000.0; R0603
R7, R8: 4700.0; R0603
R9, R11: 2200.0; R0603
R13, R14, R15, R16, R17, R18, R19, R29, R31, R32, R33, R34, R35, R36, R37, R38, R39, R58, R60, R61, R64, R65, R66: 10000.0; R0603
R20: 5.0; R0603
R21, R22: 0.1; R0603
R23, R24, R51, R56: 200.0; R0603
R25: 12100.0; R0603
R26, R27, R28, R30: 49.9; R0603
R40, R48: 120.0; R0603
R41, R42, R43, R44, R45, R46, R47, R50, R55: 100000.0; R0603
R49: 470000.0; R0603
R53: 71007.101651032; R0603
R54: 22000.0; R0603
R59: 75000.0; R0603
R62, R63: 95300.0; R0603
R67: 62000.0; R0603
U1: STM32F429IIT6; LQFP176
U2: FTSH-105-01-L-DV-K; SAMTEC_FTSH-105-01-L-DV-K
U3: LAN8710AI-EZK; QFN-32
U4: 7498011122R
U5: MAX3051EKA+T; SOT-23-8
U6, U9: 182-009-113R531; 182-009-MALE
U7: 0472192001; MOLEX_47219-2001
U8: SN65HVD230D; SOIC-8
U10: ASEK-32.768KHz-ECST; ASEK
U11: ASFL1-25MHZ-NCS; ASFL1
U12: ASFL1-50MHZ-NCS; ASFL1
U13, U15: LP3878SDX-ADJ/NOPB; WSON-8
U14: TPS54425PWP; HTSSOP14
U16: LTC2928CUHF#PBF; QFN-38_UHF
U17, U18: IRF8306MTRPbF; IRF8306MTRPBF
U19: 4-1437565-2; SW_4-1437565-2
U20: Q65110A2395; LGM67K-G1J2-24-Z
U21, U22, U23: nc7sz125m5x; NC7SZ125M5X

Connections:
CLK_U1_9: U1.9, U10.3
CLK_U1_29: U1.29, U11.3
CLK_U1_41: U1.41, U12.3
GND: C1.2, C2.2, C3.2, C4.2, C5.2, C6.2, C7.2, C8.2, C9.2, C10.2, C11.2, C12.2, C13.2, C14.2, C15.2, C16.2, C17.2, C18.2, C19.2, C20.2, C21.2, C22.2, C23.2, C24.2, C25.2, C26.2, C27.2, C28.2, C29.2, C30.2, C31.2, C32.2, C33.2, C34.2, C35.2, C36.2, C37.2, C38.2, C39.2, C40.2, C42.2, C43.2, C44.2, C45.2, C46.2, C47.2, C48.2, C49.2, C50.2, C51.2, C52.2, C53.2, C54.2, C55.2, C56.2, C57.2, C58.2, J1.2, R2.2, R20.2, R21.2, R22.2, R23.2, R25.2, R31.2, R39.2, R41.2, R49.2, R52.2, R54.2, R57.2, R59.2, R62.2, R63.2, R64.2, R65.2, R66.2, U1.14, U1.22, U1.37, U1.61, U1.71, U1.90, U1.102, U1.113, U1.126, U1.135, U1.148, U1.158, U2.3, U2.5, U3.24, U3.25, U3.EXP, U5.2, U6.5, U7.6, U7.G1, U7.G2, U7.G3, U7.G4, U8.2, U9.5, U10.2, U11.2, U12.2, U13.3, U13.PAD, U14.5, U14.8, U14.9, U14.15, U15.3, U15.PAD, U16.8, U16.9, U16.10, U16.12, U16.13, U16.24, U16.25, U16.30, U16.32, U16.39, U20.C, U21.2, U21.3, U22.1, U22.3, U23.1, U23.3
NET_U1_31: R8.1, U1.31, U23.4
NET_U1_33: R9.1, U1.33, U3.17
NET_U1_39: C19.1, C20.1, F1.1, U1.38, U1.39
NET_U1_42: R11.1, U1.42, U3.16
NET_U1_48: R16.1, U1.48
NET_U1_58: R15.1, U1.58
NET_U1_125: C22.1, U1.125
NET_U1_166: R14.1, U1.166
NET_U1_171: R13.1, U1.171
NET_U1_176: U19.3, U19.4
NET_U2_9: R20.1, U2.9
NET_U3_1: C25.1, I1.1, R26.2, R27.2, R28.2, R30.2, R33.2, U3.1, U3.27, U4.2, U4.9
NET_U3_3: R33.1, U3.3
NET_U3_7: R38.1, U3.7
NET_U3_8: R39.1, U3.8
NET_U3_9: R31.1, R32.1, U3.9
NET_U3_13: R37.1, U3.13
NET_U3_18: R29.1, U3.18
NET_U3_19: R7.1, U3.19, U22.4
NET_U3_32: R25.1, U3.32
NET_U4_1: R26.1, U3.29, U4.1
NET_U4_3: R24.2, R27.1, U3.28, U4.3
NET_U4_4: R28.1, U3.31, U4.4
NET_U4_5: C24.1, U4.2, U4.5
NET_U4_6: R30.1, U3.30, U4.6
NET_U4_8: R22.1, U4.8
NET_U4_10: R24.1, U4.10
NET_U4_11: U3.2, U4.11
NET_U4_12: R23.1, U4.12
NET_U4_13: R21.1, U4.13, U4.14
NET_U5_6: R40.2, U5.6
NET_U5_8: R41.1, U5.8
NET_U6_2: R40.2, U5.6, U6.2
NET_U6_3: R40.1, U5.7, U6.3
NET_U8_6: R48.2, U8.6
NET_U8_8: R49.1, U8.8
NET_U9_2: R48.2, U8.6, U9.2
NET_U9_3: R48.1, U8.7, U9.3
NET_U13_1: C36.1, U13.1
NET_U13_6: R51.2, R52.1, U13.6
NET_U13_8: R50.1, U13.8
NET_U14_2: R53.2, R54.1, U14.2
NET_U14_3: C39.1, U14.3
NET_U14_4: C40.1, U14.4
NET_U14_10: C41.1, I5.1, U14.10, U14.11
NET_U14_12: C41.2, U14.12
NET_U15_1: C46.1, U15.1
NET_U15_6: R56.2, R57.1, U15.6
NET_U15_8: R55.1, U15.8
NET_U16_3: R65.1, U16.3
NET_U16_6: R62.1, U16.6
NET_U16_7: R63.1, U16.7
NET_U16_16: R64.1, R67.1, U16.16
NET_U16_18: R61.1, U16.18
NET_U16_19: R60.1, U16.19, U16.20
NET_U16_21: R58.1, R59.1, U16.21, U21.4, U22.2, U23.2
NET_U16_22: C49.1, R58.2, R60.2, R61.2, U16.11, U16.22
NET_U16_26: C52.1, U16.26
NET_U16_27: C51.1, U16.27
NET_U16_28: C53.1, U16.28
NET_U16_38: R66.1, U16.38
NET_U17_3: U16.2, U17.3
NET_U18_3: U16.37, U18.3
NET_U19_1: R2.1, U19.1, U19.2
PROC_CAN1_RX: U1.11, U5.4
PROC_CAN1_TX: U1.123, U5.1
PROC_CAN2_RX: U1.92, U8.4
PROC_CAN2_TX: U1.93, U8.1
PROC_ETH_CRS_DV: R36.1, U1.53, U3.15
PROC_ETH_RXD0: R34.1, U1.54, U3.11
PROC_ETH_RXD1: R35.1, U1.55, U3.10
PROC_ETH_TXD0: U1.156, U3.22
PROC_ETH_TXD1: U1.157, U3.23
PROC_ETH_TX_EN: U1.80, U3.21
PROC_SDIO_CK: R43.1, U1.141, U7.5
PROC_SDIO_CMD: R42.1, U1.144, U7.3
PROC_SDIO_D0: R44.1, U1.117, U7.7
PROC_SDIO_D1: R45.1, U1.118, U7.8
PROC_SDIO_D2: R46.1, U1.139, U7.1
PROC_SDIO_D3: R47.1, U1.140, U7.2
PROC_SYS_JTCK_SWCLK: R18.1, U1.137, U2.4
PROC_SYS_JTDO_SWO: U1.161, U2.6
PROC_SYS_JTMS_SWDIO: R19.1, U1.124, U2.2
RST_OUT_U2_JTAG_RST_B: R17.1, U2.10, U21.1
VCC_7V9: C50.1, C54.1, C55.1, J1.1, R67.2, U16.23, U17.1, U17.2, U17.6, U17.7, U18.1, U18.2, U18.6, U18.7
VCC_S1_7V9: C37.1, C44.1, C45.1, R50.2, U13.4, U14.7, U14.13, U14.14, U17.4, U17.5
VCC_S2_7V9: C47.1, R55.2, U15.4, U18.4, U18.5
VCC_TIER1_1V2: C21.1, C26.1, C27.1, C38.1, R51.1, U1.81, U3.6, U13.5
VCC_TIER1_3V3: C1.1, C2.1, C3.1, C4.1, C5.1, C6.1, C7.1, C8.1, C9.1, C10.1, C11.1, C12.1, C13.1, C14.1, C15.1, C16.1, C17.1, C18.1, C23.1, C28.1, C29.1, C30.1, C31.1, C32.1, C33.1, C34.1, C35.1, C42.1, C43.1, C56.1, C57.1, C58.1, F1.2, I1.2, I5.2, R7.2, R8.2, R9.2, R11.2, R13.2, R14.2, R15.2, R16.2, R17.2, R18.2, R19.2, R29.2, R32.2, R34.2, R35.2, R36.2, R37.2, R38.2, R42.2, R43.2, R44.2, R45.2, R46.2, R47.2, R53.1, U1.6, U1.15, U1.23, U1.36, U1.49, U1.62, U1.72, U1.82, U1.91, U1.103, U1.114, U1.127, U1.136, U1.149, U1.159, U1.172, U2.1, U3.12, U5.3, U7.4, U8.3, U10.4, U11.4, U12.4, U14.1, U21.5, U22.5, U23.5
VCC_TIER2_1V2: C48.1, R56.1, U15.5
